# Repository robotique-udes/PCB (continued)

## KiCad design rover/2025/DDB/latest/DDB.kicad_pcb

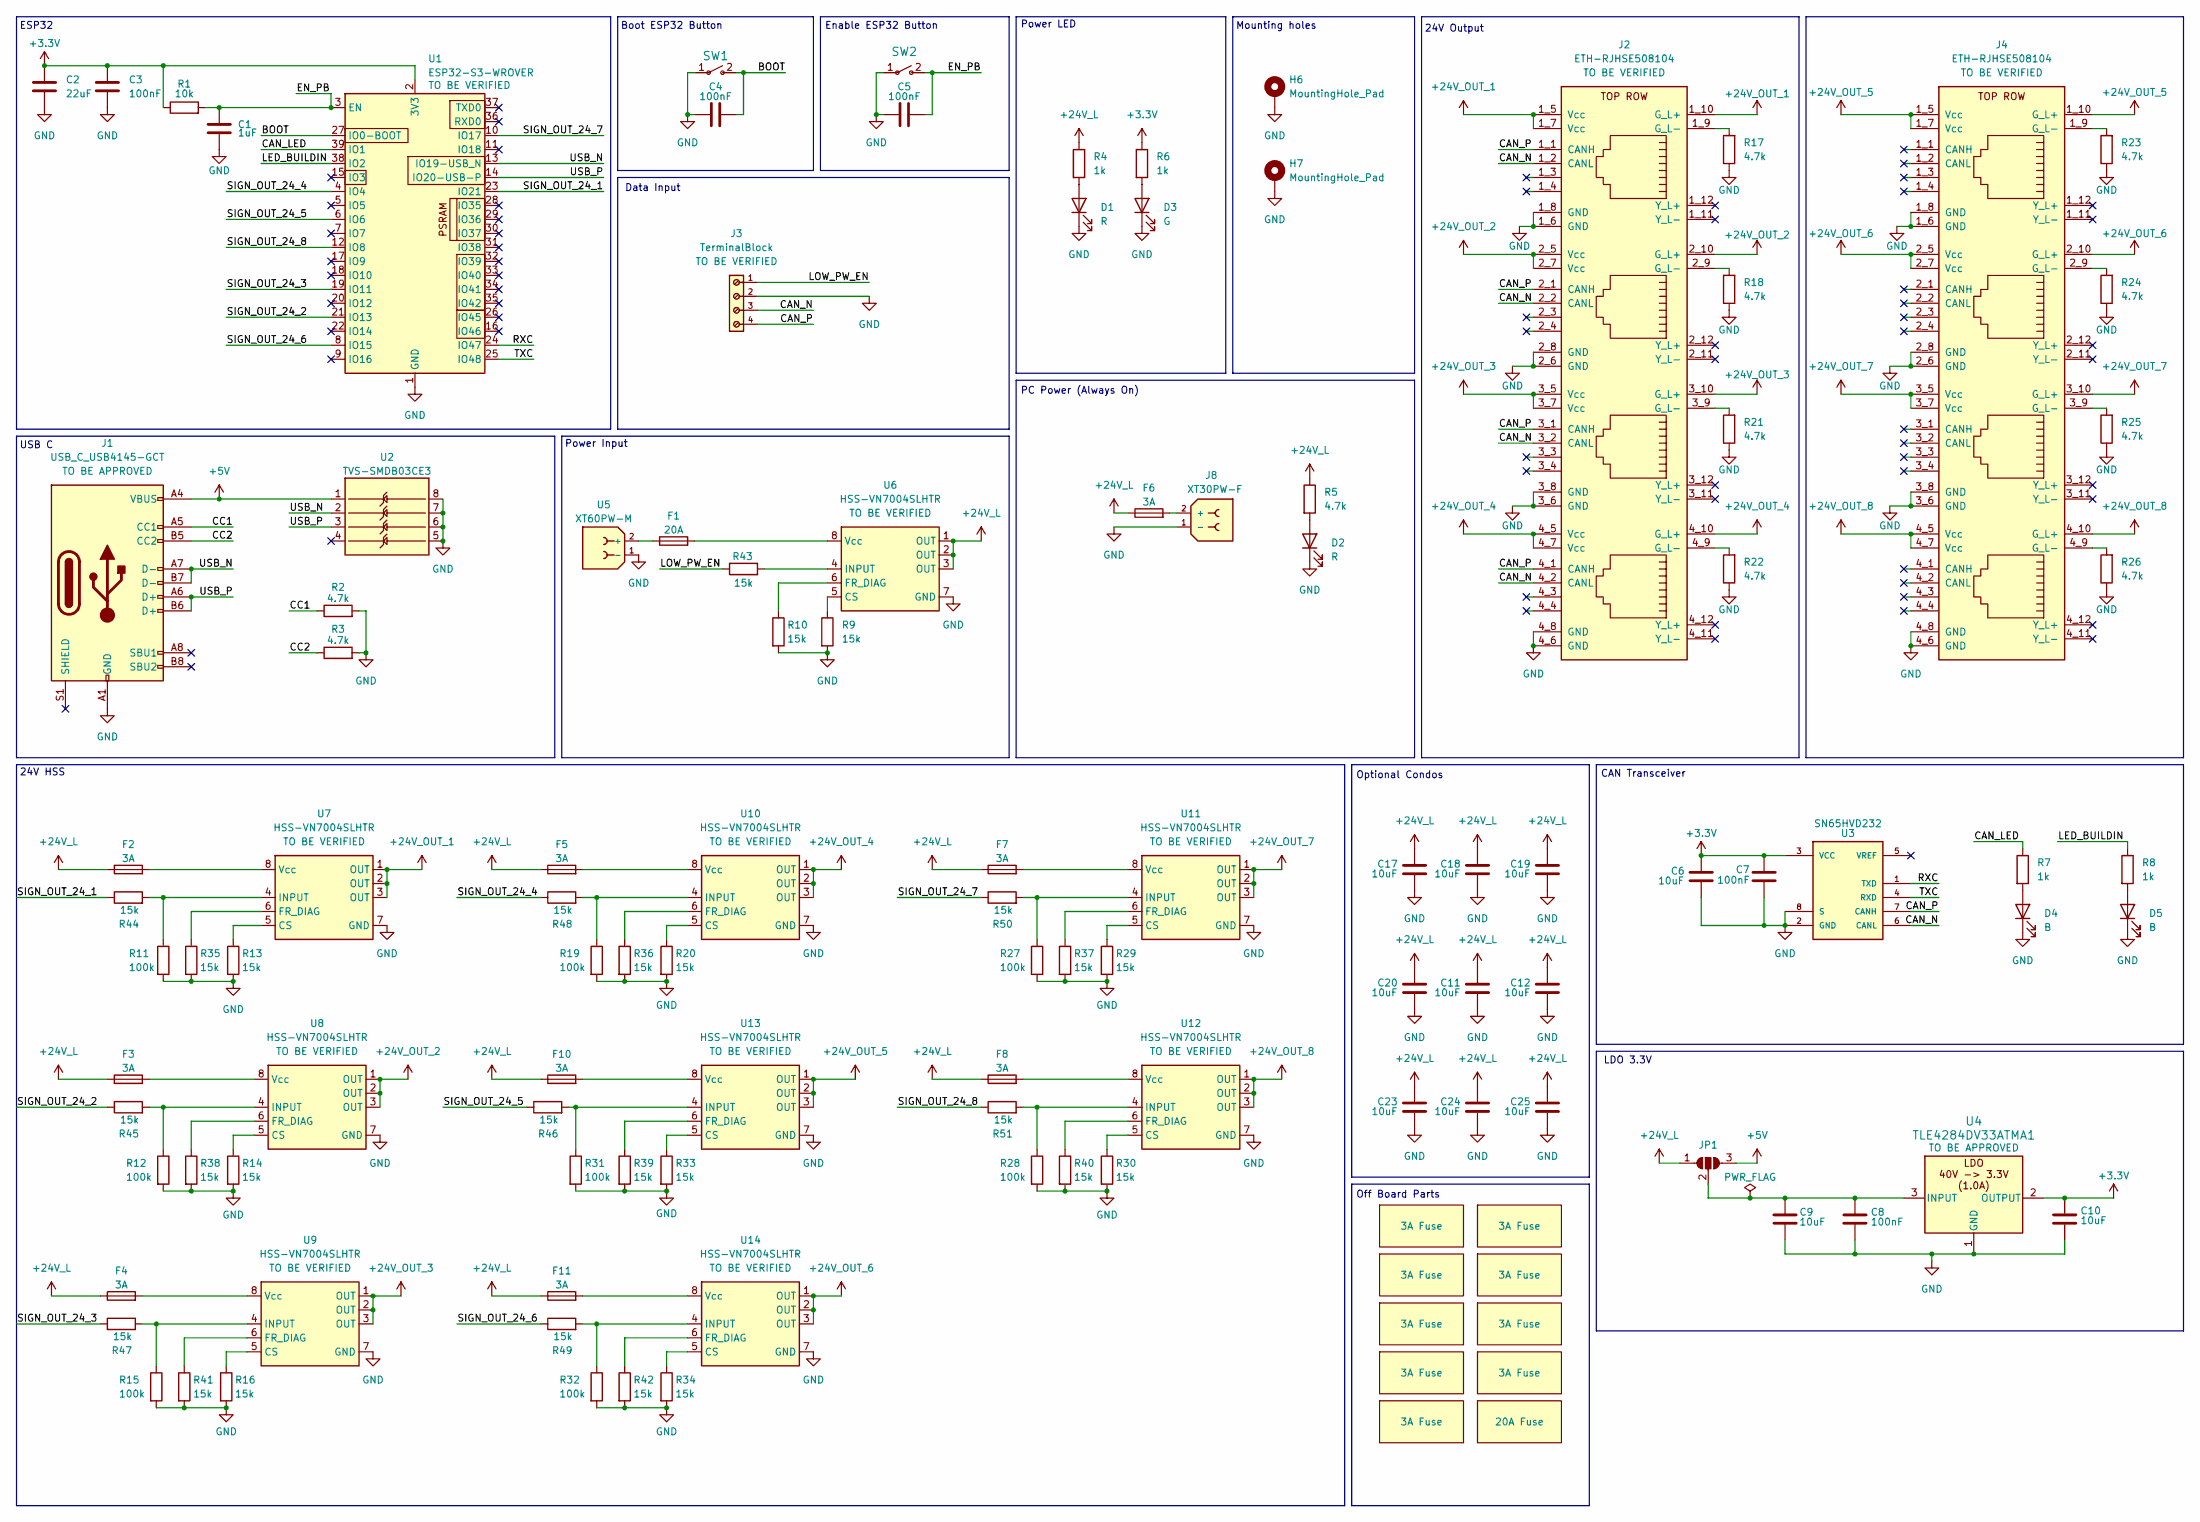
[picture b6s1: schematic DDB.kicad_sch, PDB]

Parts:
C1: 1uF; C_0805_2012Metric_Pad1.18x1.45mm_HandSolder
C2: 22uF; C_0805_2012Metric_Pad1.18x1.45mm_HandSolder
C3, C4, C5, C7, C8: 100nF; C_0805_2012Metric_Pad1.18x1.45mm_HandSolder
C6, C9, C10, C11, C12, C17, C18, C19, C20, C23, C24, C25: 10uF; C_0805_2012Metric_Pad1.18x1.45mm_HandSolder
D1, D2: R; D_0805_2012Metric_Pad1.15x1.40mm_HandSolder
D3: G; D_0805_2012Metric_Pad1.15x1.40mm_HandSolder
D4, D5: B; D_0805_2012Metric_Pad1.15x1.40mm_HandSolder
F1: 20A; FUSE_3568-20
F2, F3, F4, F5, F6, F7, F8, F10, F11: 3A; FUSE_3568-20
G1, G2, G3, G4, G5, G6, G7, G8, G9: 3A Fuse
G10: 20A Fuse
H6, H7: MountingHole_Pad; MountingHole_3.2mm_M3_DIN965_Pad_TopBottom
J1: USB_C_USB4145-GCT; USB4145_GCT
J2, J4: ETH-RJHSE508104
J3: TerminalBlock; TerminalBlock-4_P5.00mm-691137710004; PART-NUMBER 691137710004
J8: XT30PW-F; AMASS_XT30PW-F_1x02_P2.50mm_Horizontal; PARTREV 1.2
JP1: SolderJumper_3_Open; PinHeader_1x03_P2.54mm_Vertical
R1: 10k; R_0805_2012Metric_Pad1.20x1.40mm_HandSolder
R2, R3, R5, R17, R18, R21, R22, R23, R24, R25, R26: 4.7k; R_0805_2012Metric_Pad1.20x1.40mm_HandSolder
R4, R6, R7, R8: 1k; R_0805_2012Metric_Pad1.20x1.40mm_HandSolder
R9, R10, R13, R14, R16, R20, R29, R30, R33, R34, R35, R36, R37, R38, R39, R40, R41, R42, R43, R44, R45, R46, R47, R48, R49, R50, R51: 15k; R_0805_2012Metric_Pad1.20x1.40mm_HandSolder
R11, R12, R15, R19, R27, R28, R31, R32: 100k; R_0805_2012Metric_Pad1.20x1.40mm_HandSolder
SW1, SW2: TS09-63-25-WT-160-SMT-TR; SW_DIP_SPSTx01_Slide_6.7x4.1mm_W8.61mm_P2.54mm_LowProfile
U1: ESP32-S3-WROVER; ESP32-S3-WROOM-1U
U2: TVS-SMDB03CE3; SOIC-8_3.9x4.9mm_P1.27mm
U3: SN65HVD232; SOIC-8_3.9x4.9mm_P1.27mm; PARTREV 4
U4: TLE4284DV33ATMA1; TO-252-2
U5: XT60PW-M; AMASS_XT60PW-M_1x02_P7.20mm_Horizontal
U6, U7, U8, U9, U10, U11, U12, U13, U14: HSS-VN7004SLHTR; OCTAPACK_VN7004_STM-M

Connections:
+3.3V: C2.1, C3.1, C6.1, C7.1, C10.1, R1.1, R6.1, U1.2 (3V3), U3.3 (VCC), U4.2 (OUTPUT)
+5V: J1.A4 (VBUS), J1.A9 (VBUS), J1.B4 (VBUS), J1.B9 (VBUS), JP1.3 (B), U2.1
+24V_L: C11.1, C12.1, C17.1, C18.1, C19.1, C20.1, C23.1, C24.1, C25.1, F2.2, F3.2, F4.2, F5.2, F6.2, F7.2, F8.2, F10.2, F11.2, JP1.1 (A), R4.1, R5.1, U6.1 (OUT), U6.2 (OUT), U6.3 (OUT)
+24V_OUT_1: J2.1_5 (Vcc), J2.1_7 (Vcc), J2.1_10 (G_L+), U7.1 (OUT), U7.2 (OUT), U7.3 (OUT)
+24V_OUT_2: J2.2_5 (Vcc), J2.2_7 (Vcc), J2.2_10 (G_L+), U8.1 (OUT), U8.2 (OUT), U8.3 (OUT)
+24V_OUT_3: J2.3_5 (Vcc), J2.3_7 (Vcc), J2.3_10 (G_L+), U9.1 (OUT), U9.2 (OUT), U9.3 (OUT)
+24V_OUT_4: J2.4_5 (Vcc), J2.4_7 (Vcc), J2.4_10 (G_L+), U10.1 (OUT), U10.2 (OUT), U10.3 (OUT)
+24V_OUT_5: J4.1_5 (Vcc), J4.1_7 (Vcc), J4.1_10 (G_L+), U13.1 (OUT), U13.2 (OUT), U13.3 (OUT)
+24V_OUT_6: J4.2_5 (Vcc), J4.2_7 (Vcc), J4.2_10 (G_L+), U14.1 (OUT), U14.2 (OUT), U14.3 (OUT)
+24V_OUT_7: J4.3_5 (Vcc), J4.3_7 (Vcc), J4.3_10 (G_L+), U11.1 (OUT), U11.2 (OUT), U11.3 (OUT)
+24V_OUT_8: J4.4_5 (Vcc), J4.4_7 (Vcc), J4.4_10 (G_L+), U12.1 (OUT), U12.2 (OUT), U12.3 (OUT)
/BOOT: C4.2, SW1.2, U1.27 (IO0-BOOT)
/CAN_LED: R7.1, U1.39 (IO1)
/CAN_N: J2.1_2 (CANL), J2.2_2 (CANL), J2.3_2 (CANL), J2.4_2 (CANL), J3.3, U3.6 (CANL)
/CAN_P: J2.1_1 (CANH), J2.2_1 (CANH), J2.3_1 (CANH), J2.4_1 (CANH), J3.4, U3.7 (CANH)
/CC1: J1.A5 (CC1), R2.1
/CC2: J1.B5 (CC2), R3.1
/EN_PB: C1.1, C5.2, R1.2, SW2.2, U1.3 (EN)
/LED_BUILDIN: R8.1, U1.38 (IO2)
/LOW_PW_EN: J3.1, R43.1
/RXC: U1.24 (IO47), U3.1 (TXD)
/SIGN_OUT_24_1: R44.1, U1.23 (IO21)
/SIGN_OUT_24_2: R45.1, U1.21 (IO13)
/SIGN_OUT_24_3: R47.1, U1.19 (IO11)
/SIGN_OUT_24_4: R48.1, U1.4 (IO4)
/SIGN_OUT_24_5: R46.1, U1.6 (IO6)
/SIGN_OUT_24_6: R49.1, U1.8 (IO15)
/SIGN_OUT_24_7: R50.1, U1.10 (IO17)
/SIGN_OUT_24_8: R51.1, U1.12 (IO8)
/TXC: U1.25 (IO48), U3.4 (RXD)
/USB_N: J1.A7 (D-), J1.B7 (D-), U1.13 (IO19-USB_N), U2.2
/USB_P: J1.A6 (D+), J1.B6 (D+), U1.14 (IO20-USB-P), U2.3
GND: C1.2, C2.2, C3.2, C4.1, C5.1, C6.2, C7.2, C8.2, C9.2, C10.2, C11.2, C12.2, C17.2, C18.2, C19.2, C20.2, C23.2, C24.2, C25.2, D1.1 (K), D2.1 (K), D3.1 (K), D4.1 (K), D5.1 (K), H6.1, H7.1, J1.A1 (GND), J1.A12 (GND), J1.B1 (GND), J1.B12 (GND), J2.1_6 (GND), J2.1_8 (GND), J2.2_6 (GND), J2.2_8 (GND), J2.3_6 (GND), J2.3_8 (GND), J2.4_6 (GND), J2.4_8 (GND), J3.2, J4.1_6 (GND), J4.1_8 (GND), J4.2_6 (GND), J4.2_8 (GND), J4.3_6 (GND), J4.3_8 (GND), J4.4_6 (GND), J4.4_8 (GND), J8.1 (-), R2.2, R3.2, R9.2, R10.2, R11.2, R12.2, R13.2, R14.2, R15.2, R16.2, R17.1, R18.1, R19.2, R20.2, R21.1, R22.1, R23.1, R24.1, R25.1, R26.1, R27.2, R28.2, R29.2, R30.2, R31.2, R32.2, R33.2, R34.2, R35.2, R36.2, R37.2, R38.2, R39.2, R40.2, R41.2, R42.2, SW1.1, SW2.1, U1.1 (GND), U1.40 (GND), U1.41 (GND), U2.5, U2.6, U2.7, U2.8, U3.2 (GND), U3.8 (S), U4.1 (GND), U5.1 (-), U6.7 (GND), U7.7 (GND), U8.7 (GND), U9.7 (GND), U10.7 (GND), U11.7 (GND), U12.7 (GND), U13.7 (GND), U14.7 (GND)
unnamed: D1.2 (A), R4.2
unnamed: D2.2 (A), R5.2
unnamed: D3.2 (A), R6.2
unnamed: D4.2 (A), R7.2
unnamed: D5.2 (A), R8.2
unnamed: J2.1_9 (G_L-), R17.2
unnamed: J2.2_9 (G_L-), R18.2
unnamed: J2.3_9 (G_L-), R21.2
unnamed: J2.4_9 (G_L-), R22.2
unnamed: J4.1_9 (G_L-), R23.2
unnamed: J4.2_9 (G_L-), R24.2
unnamed: J4.3_9 (G_L-), R25.2
unnamed: J4.4_9 (G_L-), R26.2
unnamed: F6.1, J8.2 (+)
unnamed: C8.1, C9.1, JP1.2 (C), U4.3 (INPUT)
unnamed: F1.2, U5.2 (+)
unnamed: R9.1, U6.5 (CS)
unnamed: R10.1, U6.6 (FR_DIAG)
unnamed: R43.2, U6.4 (INPUT)
unnamed: F1.1, U6.8 (Vcc)
unnamed: R13.1, U7.5 (CS)
unnamed: R35.1, U7.6 (FR_DIAG)
unnamed: R11.1, R44.2, U7.4 (INPUT)
unnamed: F2.1, U7.8 (Vcc)
unnamed: R14.1, U8.5 (CS)
unnamed: R38.1, U8.6 (FR_DIAG)
unnamed: R12.1, R45.2, U8.4 (INPUT)
unnamed: F3.1, U8.8 (Vcc)
unnamed: R16.1, U9.5 (CS)
unnamed: R41.1, U9.6 (FR_DIAG)
unnamed: R15.1, R47.2, U9.4 (INPUT)
unnamed: F4.1, U9.8 (Vcc)
unnamed: R20.1, U10.5 (CS)
unnamed: R36.1, U10.6 (FR_DIAG)
unnamed: R19.1, R48.2, U10.4 (INPUT)
unnamed: F5.1, U10.8 (Vcc)
unnamed: R29.1, U11.5 (CS)
unnamed: R37.1, U11.6 (FR_DIAG)
unnamed: R27.1, R50.2, U11.4 (INPUT)
unnamed: F7.1, U11.8 (Vcc)
unnamed: R30.1, U12.5 (CS)
unnamed: R40.1, U12.6 (FR_DIAG)
unnamed: R28.1, R51.2, U12.4 (INPUT)
unnamed: F8.1, U12.8 (Vcc)
unnamed: R33.1, U13.5 (CS)
unnamed: R39.1, U13.6 (FR_DIAG)
unnamed: R31.1, R46.2, U13.4 (INPUT)
unnamed: F10.1, U13.8 (Vcc)
unnamed: R34.1, U14.5 (CS)
unnamed: R42.1, U14.6 (FR_DIAG)
unnamed: R32.1, R49.2, U14.4 (INPUT)
unnamed: F11.1, U14.8 (Vcc)

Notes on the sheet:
Boot ESP32 Button
Mounting holes
Off Board Parts
Data Input
ESP32
USB C
24V Output
CAN Transceiver
24V HSS
Power Input
Enable ESP32 Button
Power LED
LDO 3.3V
Optional Condos
PC Power (Always On)

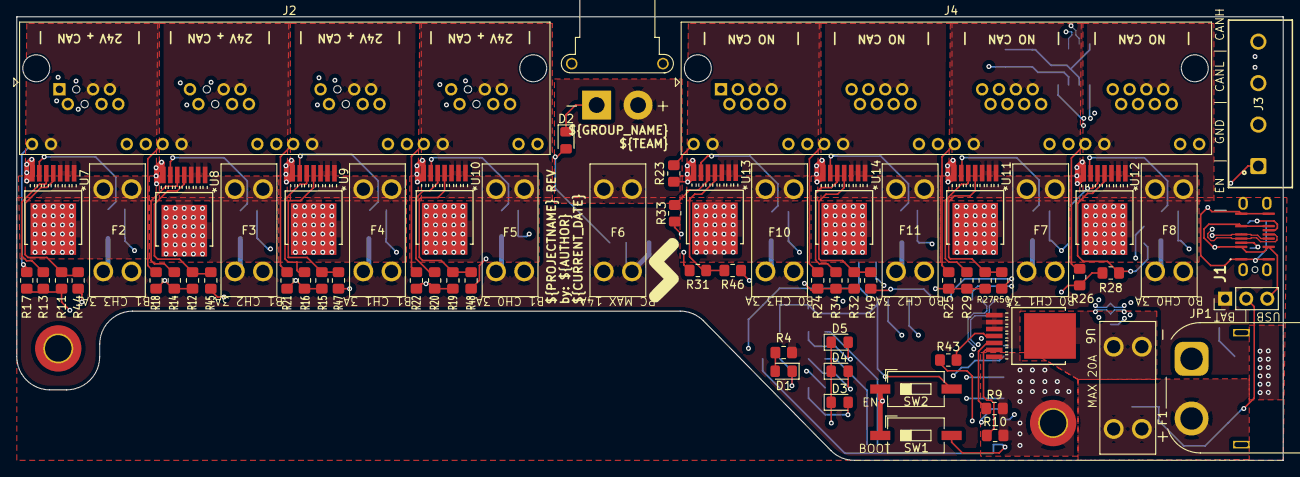
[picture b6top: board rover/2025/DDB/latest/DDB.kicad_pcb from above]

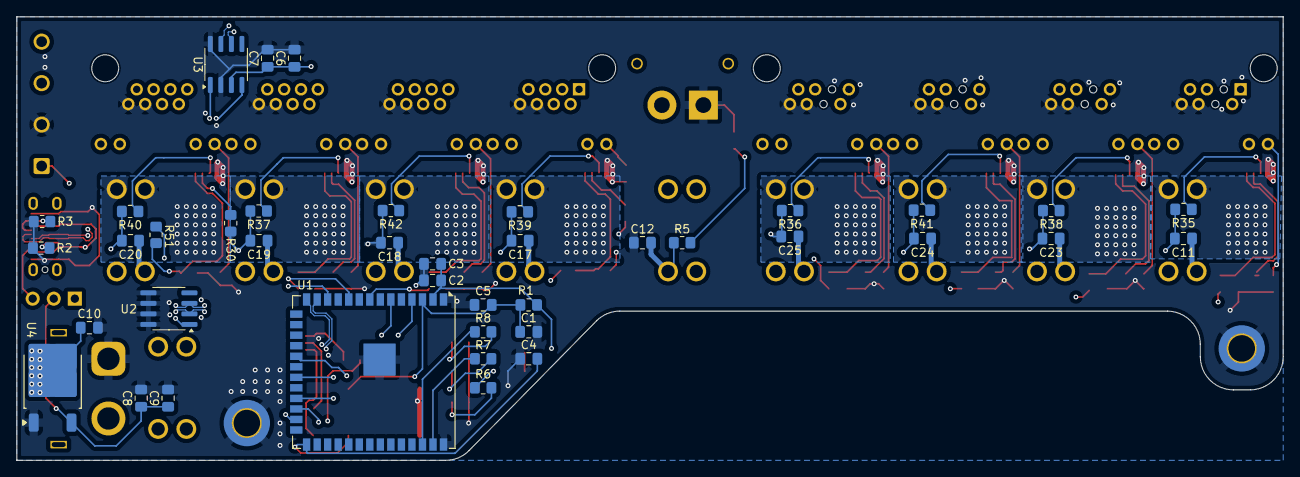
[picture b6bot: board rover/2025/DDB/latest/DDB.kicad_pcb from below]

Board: 4 copper layers, 152.8 x 53.5 mm, 109 parts (40 on the bottom side), 85 nets.

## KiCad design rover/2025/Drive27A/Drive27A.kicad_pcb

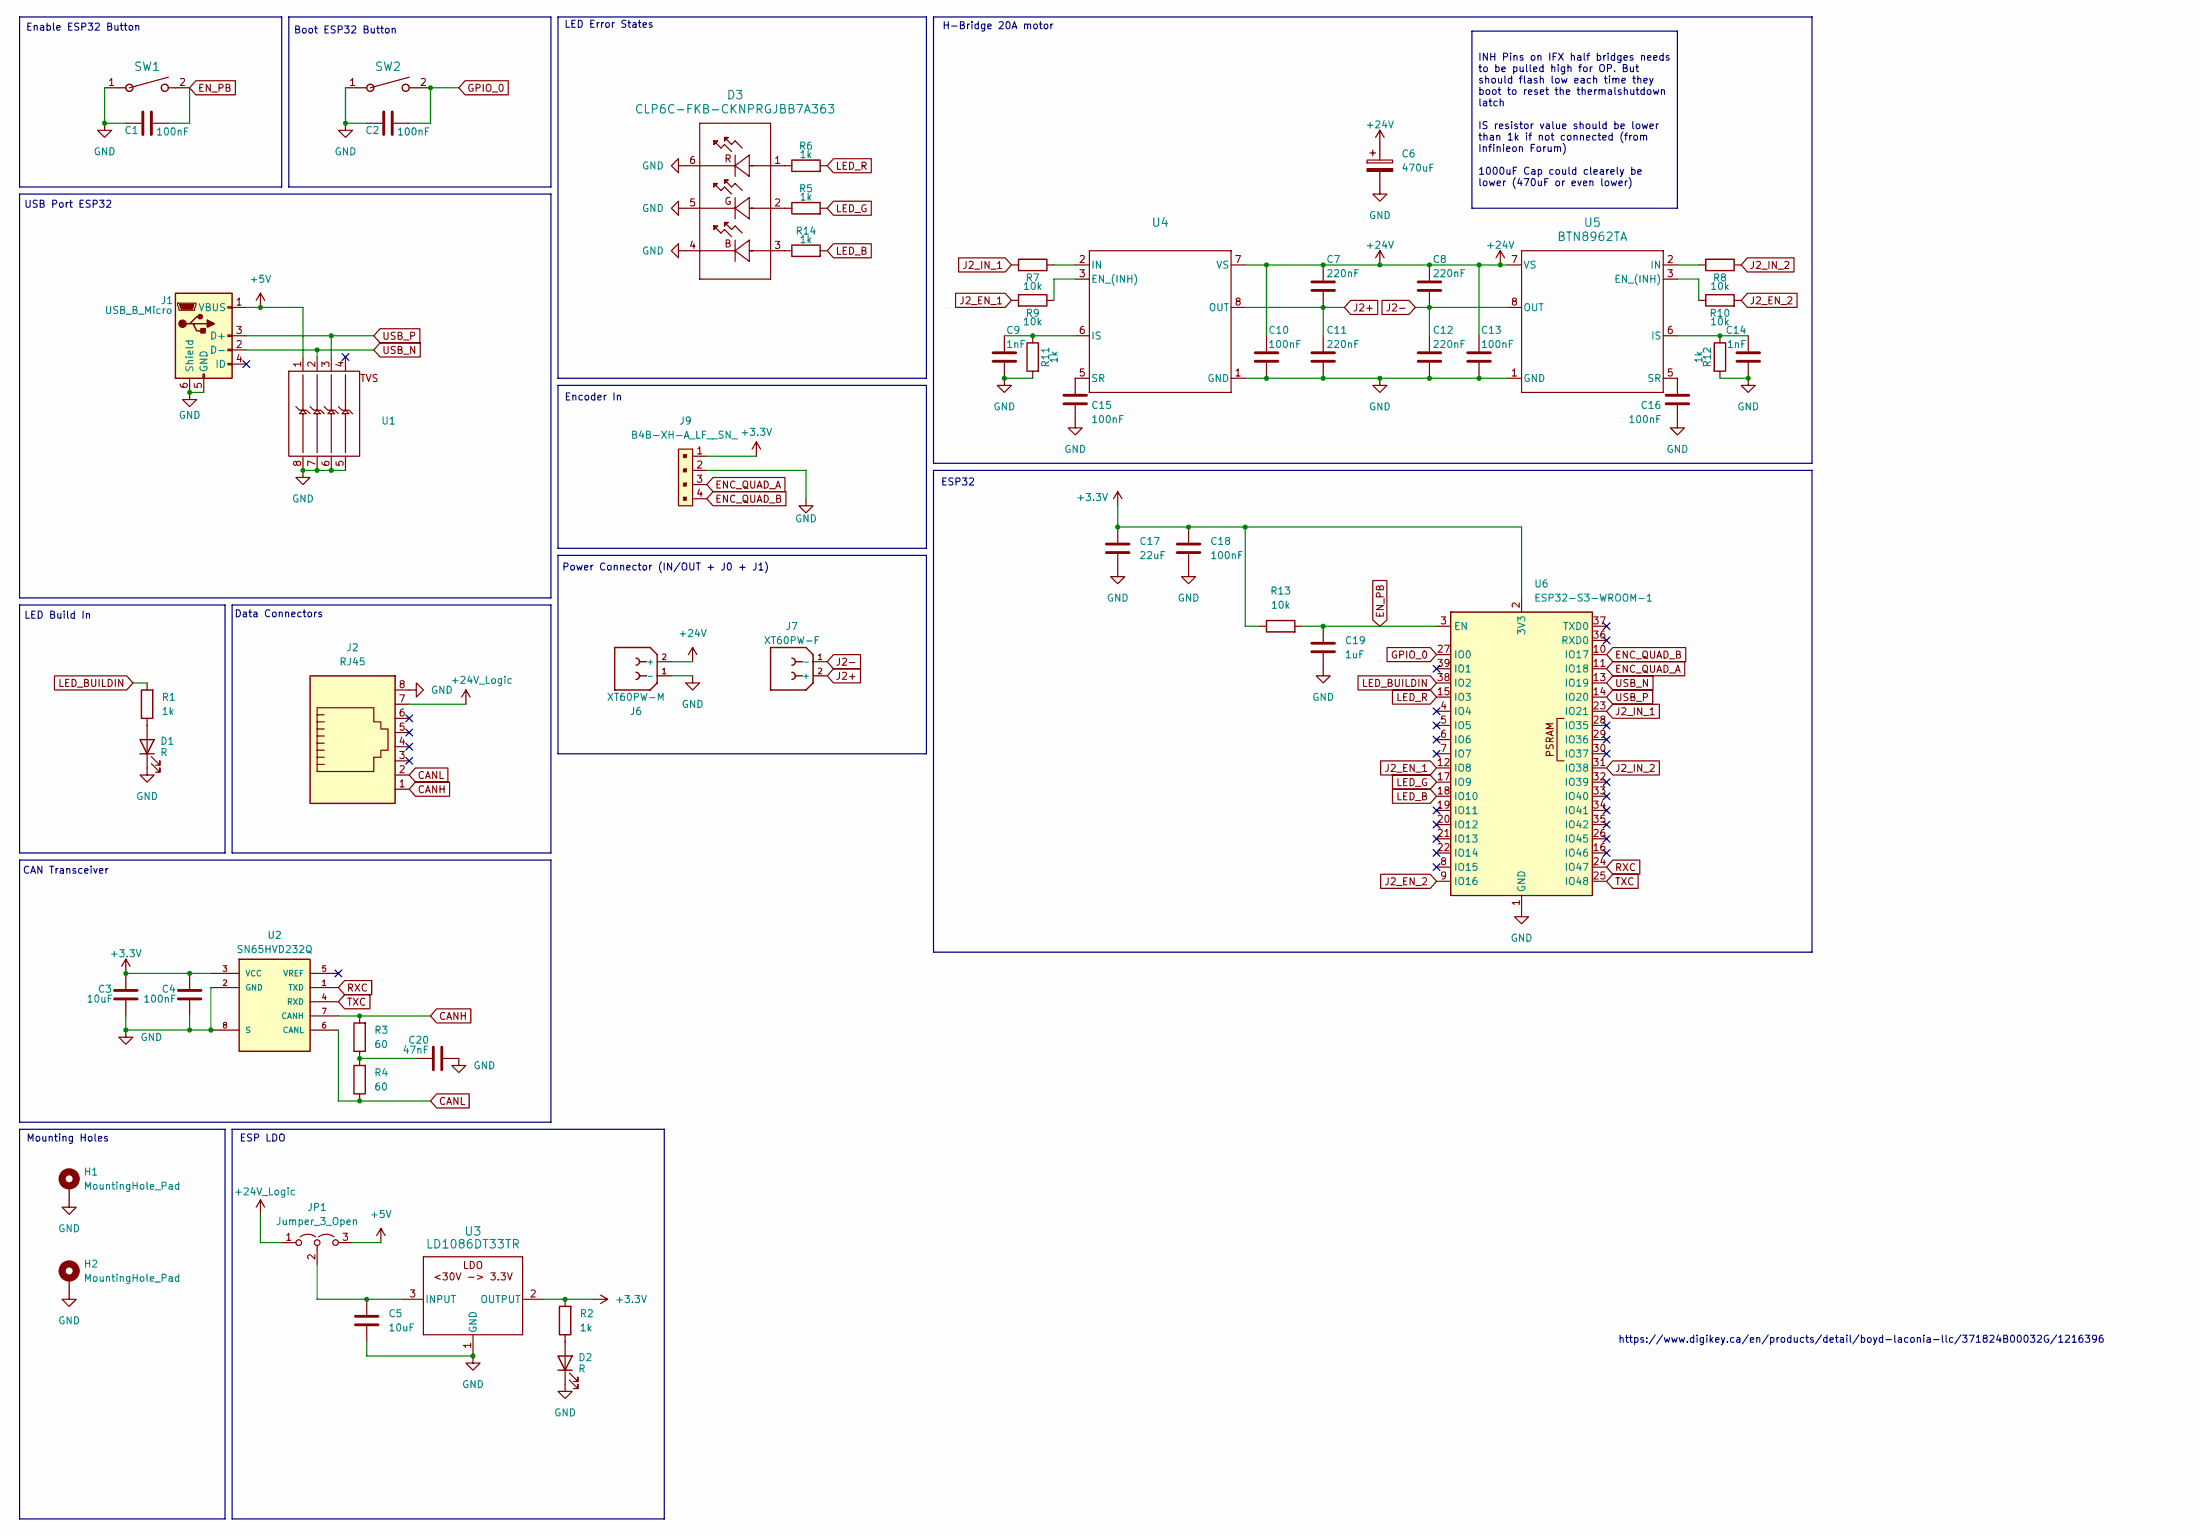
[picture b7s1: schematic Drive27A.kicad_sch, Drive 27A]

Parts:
C1, C2, C4, C10, C13, C15, C16, C18: 100nF; C_0805_2012Metric_Pad1.18x1.45mm_HandSolder; LCSC C2312829
C3, C5: 10uF; C_0805_2012Metric_Pad1.18x1.45mm_HandSolder; LCSC C440198
C6: 470uF; CP_Radial_D12.5mm_P5.00mm; LCSC C165494
C7, C8, C11, C12: 220nF; C_0805_2012Metric_Pad1.18x1.45mm_HandSolder; LCSC C86042
C9, C14: 1nF; C_0805_2012Metric_Pad1.18x1.45mm_HandSolder; LCSC C46553
C17: 22uF; C_0805_2012Metric_Pad1.18x1.45mm_HandSolder; LCSC C76634
C19: 1uF; C_0805_2012Metric_Pad1.18x1.45mm_HandSolder; LCSC C77079
C20: 47nF; C_0805_2012Metric_Pad1.18x1.45mm_HandSolder; LCSC C1777
D1, D2: R; LED_0805_2012Metric_Pad1.15x1.40mm_HandSolder; LCSC C19171391
D3: CLP6C-FKB-CKNPRGJBB7A363; CLP6C-FKB-CKNPRGJBB7A363_CRE; LCSC C7107714
H1, H2: MountingHole_Pad; MountingHole_3.2mm_M3_DIN965_Pad_TopBottom
J1: USB_B_Micro; USB_Micro-B_Amphenol_10118193-0001LF_Horizontal; LCSC C132562
J2: RJ45; AMPHENOL_54601-908WPLF; LCSC C598568
J6: XT60PW-M; AMASS_XT60PW-M_1x02_P7.20mm_Horizontal; LCSC C98732
J7: XT60PW-F; AMASS_XT60PW-F_1x02_P7.20mm_Horizontal; LCSC C428722
J9: B4B-XH-A_LF__SN_; JST_PH_B4B-PH-SM4-TB_1x04-1MP_P2.00mm_Vertical; MPN B4B-XH-A(LF)(SN); LCSC C157999
JP1: Jumper_3_Open; PinHeader_1x03_P2.54mm_Vertical
R1, R2, R5, R6, R11, R12, R14: 1k; R_0805_2012Metric_Pad1.20x1.40mm_HandSolder; LCSC C75245
R3, R4: 60; R_0805_2012Metric_Pad1.20x1.40mm_HandSolder; LCSC C2767521
R7, R8, R9, R10, R13: 10k; R_0805_2012Metric_Pad1.20x1.40mm_HandSolder; LCSC C25612
SW1, SW2: TS09-63-25-WT-160-SMT-TR; SW_TS09-63-25_CUD; LCSC C4364712
U1: SOIC-8-1EP_3.9x4.9mm_P1.27mm_EP2.29x3mm; LCSC C2448355
U2: SN65HVD232Q; SOIC127P600X175-8N; PARTREV 4; LCSC C2859712
U3: LD1086DT33TR; TO252-2_AZ1117ID-3.3TRG1_DIO-L; LCSC C12051
U4, U5: BTN8962TA; PG-TO263-7-1_INF-M; LCSC C534738
U6: ESP32-S3-WROOM-1; LCSC C2913198

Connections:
+3.3V: C3.1, C4.1, C17.1, C18.1, J9.1, R2.2, R13.1, U2.3 (VCC), U3.2 (OUTPUT), U6.2 (3V3)
+5V: J1.1 (VBUS), JP1.3 (B), U1.1
+24V: C6.1, C7.1, C8.1, C10.1, C13.1, J6.2 (+), U4.7 (VS), U5.7 (VS)
+24V_Logic: J2.7, JP1.1 (A)
CANH: J2.1, R3.2, U2.7 (CANH)
CANL: J2.2, R4.1, U2.6 (CANL)
ENC_QUAD_A: J9.3, U6.11 (IO18)
ENC_QUAD_B: J9.4, U6.10 (IO17)
EN_PB: C1.2, C19.1, R13.2, SW1.2, U6.3 (EN)
GND: C1.1, C2.1, C3.2, C4.2, C5.2, C6.2, C9.2, C10.2, C11.2, C12.2, C13.2, C14.2, C15.2, C16.2, C17.2, C18.2, C19.2, C20.1, D1.1 (K), D2.1 (K), D3.4, D3.5, D3.6, H1.1, H2.1, J1.5 (GND), J1.6 (Shield), J2.8, J6.1 (-), J9.2, R11.2, R12.2, SW1.1, SW2.1, U1.5, U1.6, U1.7, U1.8, U2.2 (GND), U2.8 (S), U3.1 (GND), U4.1 (GND), U5.1 (GND), U6.1 (GND), U6.40 (GND), U6.41 (GND)
GPIO_0: C2.2, SW2.2, U6.27 (IO0)
J2+: C7.2, C11.1, J7.2 (+), U4.8 (OUT)
J2-: C8.2, C12.1, J7.1 (-), U5.8 (OUT)
J2_EN_1: R9.2, U6.12 (IO8)
J2_EN_2: R10.2, U6.9 (IO16)
J2_IN_1: R7.2, U6.23 (IO21)
J2_IN_2: R8.2, U6.31 (IO38)
LED_B: R14.2, U6.18 (IO10)
LED_BUILDIN: R1.2, U6.38 (IO2)
LED_G: R5.2, U6.17 (IO9)
LED_R: R6.2, U6.15 (IO3)
unnamed: C20.2, R3.1, R4.2
unnamed: D1.2 (A), R1.1
unnamed: D2.2 (A), R2.1
unnamed: D3.1, R6.1
unnamed: D3.2, R5.1
unnamed: D3.3, R14.1
unnamed: C5.1, JP1.2 (C), U3.3 (INPUT)
unnamed: R9.1, U4.3 (EN_(INH))
unnamed: R7.1, U4.2 (IN)
unnamed: C9.1, R11.1, U4.6 (IS)
unnamed: C15.1, U4.5 (SR)
unnamed: R10.1, U5.3 (EN_(INH))
unnamed: R8.1, U5.2 (IN)
unnamed: C14.1, R12.1, U5.6 (IS)
unnamed: C16.1, U5.5 (SR)
RXC: U2.1 (TXD), U6.24 (IO47)
TXC: U2.4 (RXD), U6.25 (IO48)
USB_N: J1.2 (D-), U1.2, U6.13 (IO19)
USB_P: J1.3 (D+), U1.3, U6.14 (IO20)

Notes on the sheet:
INH Pins on IFX half bridges needs to be pulled high for OP. But should flash low each time they boot to reset the thermalshutdown latch IS resistor value should be lower than 1k if not connected (from Infinieon Forum) 1000uF Cap could clearely be lower (470uF or even lower)
Boot ESP32 Button
LED Build In
Enable ESP32 Button
CAN Transceiver
Encoder In
LED Error States
Power Connector (IN/OUT + J0 + J1)
ESP LDO
Data Connectors
H-Bridge 20A motor
Mounting Holes
USB Port ESP32
https://www.digikey.ca/en/products/detail/boyd-laconia-llc/371824B00032G/1216396
ESP32

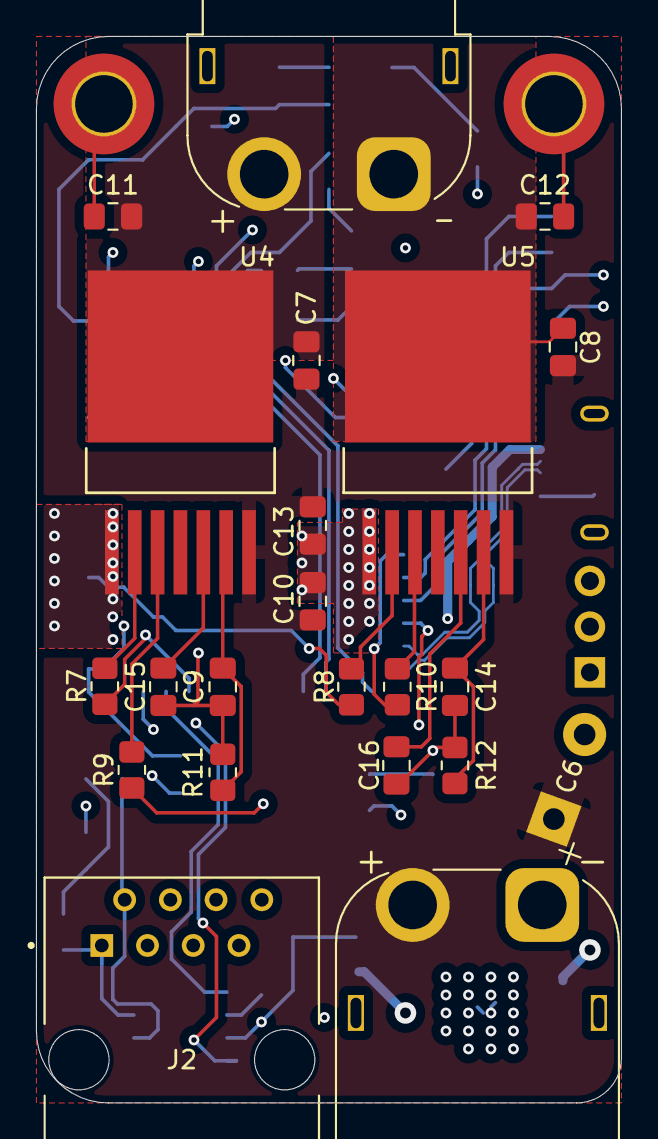
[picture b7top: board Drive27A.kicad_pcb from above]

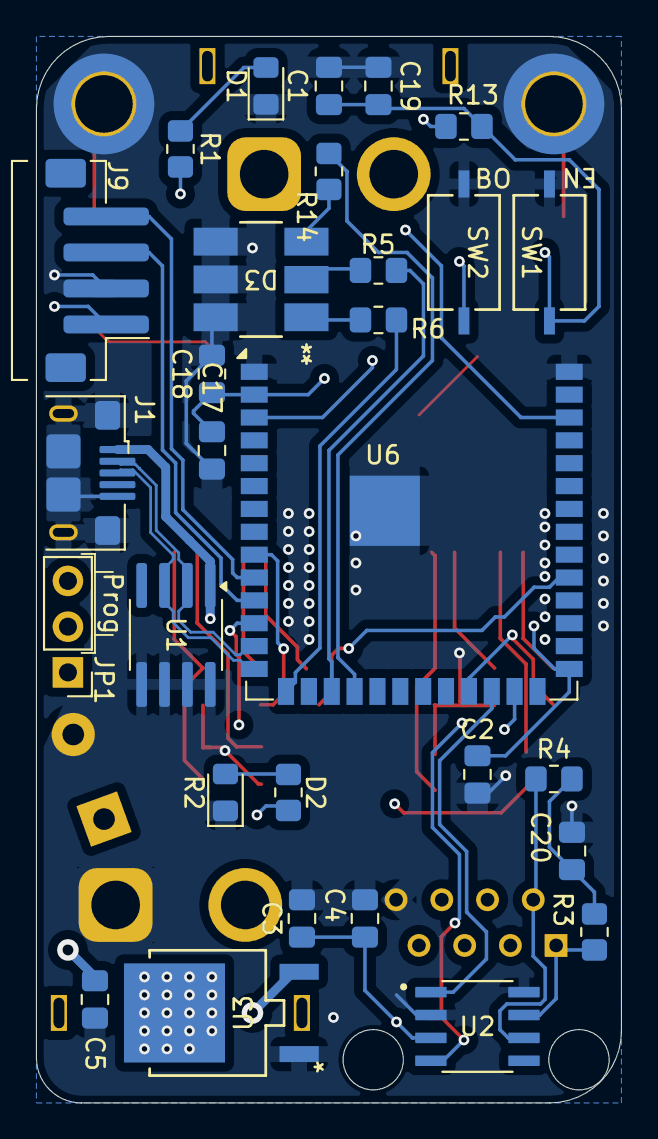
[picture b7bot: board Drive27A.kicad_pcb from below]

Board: 4 copper layers, 32.5 x 59.3 mm, 53 parts (29 on the bottom side), 40 nets.
